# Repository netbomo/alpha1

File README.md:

alpha1
======

Prototype de shield pour arduino, permettant de monitorer une éolienne.

Voir les premières données :

http://desplanchesdepalette.org/colibri/Colibri_Energie.html

Projet :
--------

Le but est de créer une shield pouvant par exemple créer un node pour le système OpenEnergyMonitor ou se greffant sur une carte Akeru, une carte Arduino Yun...

###Capteur désirés :

- Anémomètre
- girouette
- capteur de courant
- capteur de tension 

note : Pour l'instant ma carte emontx ne fontionne plus, et la sonde de courant CT ne donne plus de valeur correcte, donc nous utilisons un WattNode Pulse ainsi qu'une carte arduino UNO.

###Etat des lieux :
 Le systême fonctionne à l'atelier, mais pose problème en situation, la présence proche du réseau à l'air d'en être la cause. La prochaine modification sera de mettre le systême dans un boitier métalique avec une mise à la masse. Une carte de meilleure qualité devrait aider aussi.

Le premier prototype est installé avec la version du programme netbomo.ino

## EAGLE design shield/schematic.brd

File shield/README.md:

Caractéristiques recherchées pour le shield :
=============================================

- connectique pour la carte arduino UNO
- 2 interfaces anémomètres
- 1 interface girouette
- 1 capteur de tension comme sur le système Open Energy Monitor
- 1 CT (mesures de courant) comme sur le système Open Energy Monitor

Avoir la possibilité de mettre un modem rfm12b pour être utilisée dans le cadre du projet Open Energy Monitor

Shield caracteristics : 
=======================

- Arduino connectics
- 2 anemometer inputs
- 1 wind vane input
- 1 Voltage sensor
- 1 current sensor
- RFM12B connectics

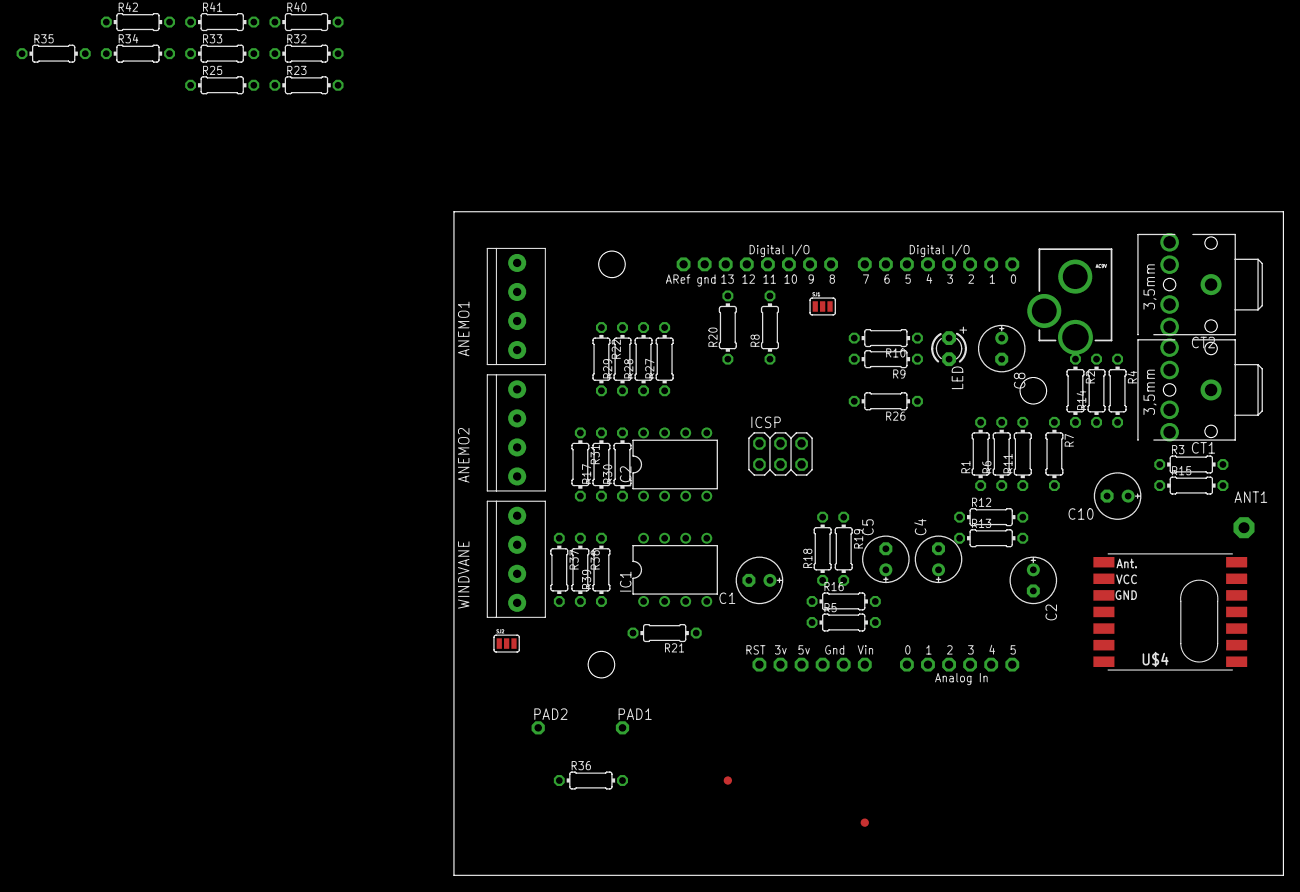
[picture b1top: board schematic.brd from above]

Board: 2 copper layers, 100.0 x 80.0 mm, 66 parts (0 on the bottom side), 45 nets, no tracks yet.

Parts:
AC9V: POWER_JACKPTH_LOCK; POWER_JACK_PTH_LOCK
ANEMO1, ANEMO2: 1X4-3.5MM; 1X04-3.5MM
ANT1: PAD-01
C1, C8, C10: 10µ; E2,5-6E
C2: 0.1µ; E2,5-6E
C4, C5: 0.1u; E2,5-6E
CT1, CT2: STEREOJACK; STX3100
IC1, IC2: LM358N; DIL08
ICSP: 3x2F - BOTTOM; 2X03
LED: LED3MM
PAD1, PAD2: JEELABS_1,6/0,8
R1, R2, R4, R6, R11, R12: 470K; 0204/7
R3, R5, R15, R16: 33R; 0204/7
R7, R9, R17, R19, R21, R22, R23, R25, R28, R31, R32, R34, R37, R40, R41: 10k; 0204/7
R8, R18, R20: 4k7; 0204/7
R10: 470R; 0204/7
R13: 100K; 0204/7
R14: 10K; 0204/7
R26, R30, R33, R35, R39, R42: 100k; 0204/7
R27, R36: 1M; 0204/7
R29, R38: 12k; 0204/7
SJ1, SJ2: SJ_3
U$1, U$3: FIDUCIAL; FIDUCIAL_1MM
U$2: ARDUINO-BPLACE
U$4: RFM12B
WINDVANE: 1X4-3.5MM; 1X04-3.5MM

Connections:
3.3V: C2.+, U$2.3V, U$4.VDD
+5V: IC1.8, IC2.8, ICSP.2, R4.2, R6.2, R11.2, R17.2, R22.2, R23.2, R26.1, R35.1, U$2.5V
ADC0: R13.2, R14.1, U$2.A0
ADC1: CT1.1, R5.2, R16.2, U$2.A1
ADC2: CT2.1, R3.2, R15.2, U$2.A2
ADC3: U$2.A3, WINDVANE.2
ANEMO1A: ANEMO1.1, R31.1
ANEMO1B: ANEMO1.2, R32.1
ANEMO2: ANEMO2.3, IC1.7, R23.1, R36.2, SJ2.1
ANEMO2A: ANEMO2.1, R40.1
ANEMO2B: ANEMO2.2, R41.1
DIG2: SJ2.2, U$2.D2
DIG3: ANEMO1.3, IC2.7, R22.1, R27.2, U$2.D3
DIG5: SJ1.3, U$2.D5
DIG9: R10.2, U$2.D9
DIG10: SJ1.1, U$2.D10
GND: ANEMO1.4, ANEMO2.4, C1.-, C2.-, C4.-, C5.-, C8.-, C10.-, CT1.4, CT2.4, IC1.4, IC2.4, ICSP.6, LED.K, R1.2, R2.2, R7.1, R9.1, R12.1, R19.1, R21.1, R25.2, R33.2, R34.2, R42.2, U$2.GND, U$2.GND1, U$2.GND2, U$4.GND, WINDVANE.4
MISO: ICSP.1, U$2.D12, U$4.SDO
MOSI: ICSP.4, R8.2, U$2.D11
unnamed: PAD2.1, SJ2.3, U$4.IRQ
unnamed: PAD1.1, R18.2, SJ1.2
unnamed: R17.1, WINDVANE.1
unnamed: R21.2, WINDVANE.3
unnamed: AC9V.PWR, R13.1
unnamed: IC2.3, R31.2, R33.1
unnamed: IC2.2, R30.1, R32.2
unnamed: IC2.1, R29.1, R30.2
unnamed: C4.+, R28.2, R29.2
unnamed: IC2.6, R28.1
unnamed: IC2.5, R25.1, R26.2, R27.1
unnamed: IC1.3, R40.2, R42.1
unnamed: IC1.2, R39.1, R41.2
unnamed: IC1.1, R38.1, R39.2
unnamed: C5.+, R37.2, R38.2
unnamed: IC1.5, R37.1
unnamed: IC1.6, R34.1, R35.2, R36.1
unnamed: C8.+, CT2.5, R2.1, R3.1, R4.1, R15.1
unnamed: AC9V.GND, C10.+, R11.1, R12.2, R14.2
unnamed: C1.+, CT1.5, R1.1, R5.1, R6.1, R16.1
unnamed: LED.A, R10.1
unnamed: ANT1.1, U$4.ANT
unnamed: R7.2, R20.1, U$4.SCK
unnamed: R8.1, R9.2, U$4.SDI
unnamed: R18.1, R19.2, U$4.SEL
SCK: ICSP.3, R20.2, U$2.D13

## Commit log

2014-06-20 edit README.md
2014-06-20 add Raspberry conf
2014-06-20 edit raspberryConf/README.md
2014-06-20 test
2014-06-20 init commit
2014-06-20 summit
2014-06-20 add 3Gtest
2014-06-24 add schematic
2014-07-04 add netbomo ino
2014-08-08 The windWane representation has been modified
2014-12-04 clean in repositories
2014-12-04 Updade *.ino
2014-12-04 Add Display files
2014-12-16 update kicad files
2015-03-13 test yasin
